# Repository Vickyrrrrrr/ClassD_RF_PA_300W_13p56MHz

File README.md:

# 300W 13.56MHz Class-D RF Power Amplifier

For hackerfab lithography machine RF plasma source.

## Design Renders

### Schematic

### PCB Layout

## What This Is

A 300W, 13.56MHz Class-D RF power amplifier based on the El-Hamamsy half-bridge
topology. Designed and simulated in Cadence Spectre (305W output, 83.7%
efficiency), then translated to a KiCAD 10 PCB project for fabrication.

## Quick Start

### 1. Open the KiCAD project
```bash
# Install KiCAD 10 (if not already installed)
# Linux: download AppImage from https://www.kicad.org/download/linux/
# Windows/Mac: download from https://www.kicad.org/download/

# Open the project
kicad kicad/rf_pa_300w.kicad_pro
```

### 2. Verify the PCB layout
The PCB is fully routed, zone-refilled, and ERC/DRC clean:
- **Ground plane**: Bottom layer (`B.Cu`) is filled with solid `GND` copper.
- **Routing**: Top layer (`F.Cu`) and bottom layer (`B.Cu`) traces are fully complete.
- **Verification**: DRC and ERC checks have zero active electrical violations.
- **Gerbers**: Fabrication-ready Gerbers have been generated in `kicad/gerbers.zip`.

See `docs/kicad_build_report.md` for detailed results.

### 3. Order the PCB
- Send `kicad/gerbers/` folder to JLCPCB, PCBWay, or OSH Park
- Settings: 2-layer, 1.6mm FR4, HASL finish, 80x50mm
- Cost: ~$5 for 5 boards

### 4. Order parts
See `docs/bom.md` for complete parts list (~$92 total including power supplies).

### 5. Assemble
See `docs/pcb_layout.md` for component placement and assembly notes.

### 6. Test
1. Apply 12V VCC only (no 72.5V Vdd)
2. Check gate drive waveforms on oscilloscope (HIN, LIN, HO, LO)
3. Apply 72.5V Vdd
4. Measure RF output at SMA connector
5. Tune dead time for ZVS (~19ns needed, see `docs/gate_driver_spec.md`)

## Project Structure

```
ClassD_RF_PA_300W_13p56MHz/
├── README.md                  # This file - START HERE
├── docs/
│   ├── build_report.md        # Full simulation build report (Spectre)
│   ├── kicad_build_report.md  # KiCAD PCB design report
│   ├── gate_driver_spec.md    # IR2181S gate driver specification
│   ├── bom.md                 # Bill of materials (~$92)
│   └── pcb_layout.md          # PCB layout guide and matching network
├── kicad/
│   ├── rf_pa_300w.kicad_pro   # KiCAD 10 project file
│   ├── rf_pa_300w.kicad_sch   # Schematic (25 components, generated)
│   ├── rf_pa_300w.kicad_pcb   # PCB (80x50mm, 21 footprints, ratsnest + B.Cu GND pour)
│   ├── gen_schematic.py       # Schematic generator script
│   ├── gen_pcb.py             # PCB generator script
│   ├── schematic.pdf          # Schematic PDF
│   ├── pcb_layout.pdf         # PCB layout PDF
│   └── gerbers/               # Fabrication files
│       ├── *.gbr              # Gerber layer files
│       ├── *.drl              # Drill files
│       └── pos.csv            # Pick-and-place positions
├── netlists/
│   ├── classd_pa.scs          # Spectre netlist (IRF540 Level-3, bootstrap)
│   └── analyze_results.py     # Python simulation analysis
├── models/
│   └── irf540.mod             # IRF540 SPICE model
└── results/
    └── classd_irf540_bs_ascii # Final simulation output (305W, 83.7%)
```

## Circuit Design

### Topology
- **Half-bridge Class-D** with 2x IRF540 NMOS power MOSFETs
- **IR2181S** bootstrap gate driver (SOIC-8)
- **LC tank**: 300nH series L, 470pF shunt C, 2.55Ω load
- **L-match network**: 130nH series L, 1nF shunt C (2.55Ω → 50Ω)

### Key Design Parameters

| Parameter | Value |
|-----------|-------|
| Output power | 305W (simulated) |
| Frequency | 13.56MHz |
| Efficiency | 83.7% (simulated) |
| Vdd (power stage) | 72.5V |
| VCC (gate driver) | 12V |
| Dead time | 11.5ns (needs tuning to ~19ns for full ZVS) |
| Load resistance | 2.55Ω |
| RF output impedance | 50Ω (via L-match) |

### Component List (21 components on PCB)

| Ref | Part | Value | Package |
|-----|------|-------|---------|
| U1 | IR2181S | Gate driver | SOIC-8 |
| Q1, Q2 | IRF540 | NMOS power | TO-220 |
| D1 | UF4007 | Bootstrap diode | DO-41 |
| D2, D3 | 1N5819 | Schottky bypass | DO-41 |
| R1, R2 | 2.2Ω | Gate resistors | 1206 SMD |
| R3 | 2.55Ω | Load resistor | THT |
| C1 | 100uF | Vdd bulk cap | Radial THT |
| C2, C3 | 0.1uF | Decoupling | 1206 SMD |
| C4 | 220nF | Bootstrap cap | 1206 SMD |
| C5 | 470pF | Tank cap | 1206 SMD |
| C6 | 1nF | Match cap | 1206 SMD |
| L1 | 300nH | Tank inductor | THT (custom wound) |
| L2 | 130nH | Match inductor | THT (custom wound) |
| J1 | Terminal block | Vdd 72.5V input | 5mm pitch |
| J2 | SMA | RF output 50Ω | Edge mount |
| J3 | Terminal block | VCC 12V input | 5mm pitch |
| J4 | Pin header | PWM input (HIN, LIN) | 2.54mm |

## PCB Specifications

| Parameter | Value |
|-----------|-------|
| Board size | 80mm x 50mm |
| Layers | 2 (F.Cu top, B.Cu bottom ground plane) |
| Material | FR4, 1.6mm, 1oz copper |
| Finish | HASL |
| RF traces | 50Ω impedance controlled (3.06mm width) |
| Power traces | 3.0mm (Vdd, MID switching node) |
| Min trace width | 0.25mm |
| Min clearance | 0.2mm |

## Simulation Results

The amplifier was simulated in Cadence Spectre 14.1 using a real IRF540
Level-3 SPICE model with bootstrap gate drive:

- **Output power**: 305W
- **Drain efficiency**: 83.7%
- **Frequency**: 13.56MHz
- **0 simulation errors**

The root cause of a 7-week simulation failure was identified as the gate
drive being referenced to GND instead of the mid (switching) node. With
bootstrap gate drive (Vgs referenced to mid), the simulation works correctly.

See `docs/build_report.md` for the full simulation methodology and debugging.

## What's Left To Do

1. **Order PCB**: Upload [gerbers.zip](file:///C:/Users/VICKY/.gemini/antigravity/scratch/gerbers.zip) to a manufacturer (JLCPCB, PCBWay, OSH Park).
2. **Order parts**: Use BOM from `docs/bom.md` (~$92 total).
3. **Wind custom inductors**: Wind L1 ($300\text{ nH}$) and L2 ($130\text{ nH}$) (see `docs/pcb_layout.md` for specs).
4. **Assemble PCB**: Solder parts, mount heatsinks on `Q1` & `Q2`.
5. **Test**: Apply 12V VCC first, verify gate signals, then apply 72.5V Vdd.
6. **Tune dead time**: Tune dead time for Zero Voltage Switching (ZVS) on scope (~19ns target).

## Documentation Index

| Document | What's in it |
|----------|-------------|
| `README.md` (this file) | Project overview, quick start, component list |
| `docs/build_report.md` | Full simulation report (Spectre, IRF540, debugging) |
| `docs/kicad_build_report.md` | KiCAD PCB design report (format, DRC, Gerbers) |
| `docs/gate_driver_spec.md` | IR2181S gate driver circuit, bootstrap, timing |
| `docs/bom.md` | Complete bill of materials with KiCAD refs |
| `docs/pcb_layout.md` | PCB layout guide, trace widths, matching network |

## Tools Used

- **Cadence Spectre 14.1** — circuit simulation
- **KiCAD 10.0.4** — schematic capture and PCB layout
- **Python 3** — simulation analysis and KiCAD file generation
- **OS**: RHEL 8.10 WSL2 on Windows 11

## License

Open source hardware design for hackerfab lithography machine.

---

*Project date: 2026-06-29*
*Simulation: 305W at 83.7% efficiency*
*KiCAD: fully routed schematic and PCB; ERC/DRC verified and fabrication Gerbers generated.*

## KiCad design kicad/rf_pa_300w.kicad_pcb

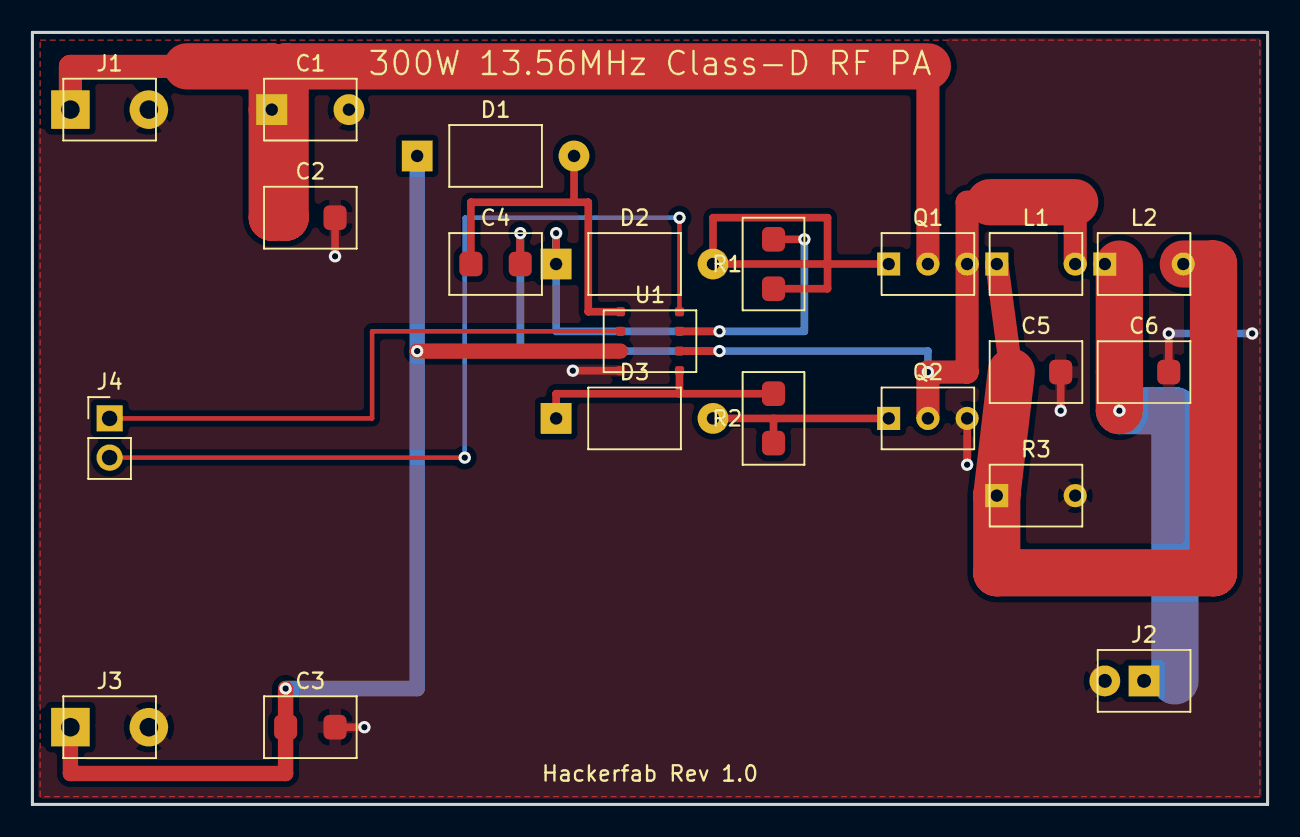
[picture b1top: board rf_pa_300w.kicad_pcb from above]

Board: 2 copper layers, 80.0 x 50.0 mm, 21 parts (0 on the bottom side), 13 nets.

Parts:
C1: 100uF; CP_Radial_D10.0mm_P5.00mm
C2, C3: 0.1uF; C_1206_3216Metric
C4: 220nF; C_1206_3216Metric
C5: 470pF; C_1206_3216Metric
C6: 1nF; C_1206_3216Metric
D1: UF4007; D_DO-41_SOD81_P10.16mm_Horizontal
D2, D3: 1N5819; D_DO-41_SOD81_P10.16mm_Horizontal
J1: Vdd 72.5V; TerminalBlock_bornier-2_P5.0mm
J2: SMA 50ohm; SMA_Amphenol_132289_EdgeMount
J3: VCC 12V; TerminalBlock_bornier-2_P5.0mm
J4: PWM IN; PinHeader_1x02_P2.54mm_Vertical
L1: 300nH; L_Axial_L7.0mm_D3.3mm_P5.08mm_Vertical
L2: 130nH; L_Axial_L7.0mm_D3.3mm_P5.08mm_Vertical
Q1, Q2: IRF540; TO-220-3_Vertical
R1, R2: 2.2; R_1206_3216Metric
R3: 2.55; R_Axial_DIN0309_L9.0mm_D3.2mm_P5.08mm_Vertical
U1: IR2181S; SOIC-8_3.9x4.9mm_P1.27mm

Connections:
+72V5: C1.1, C2.1, J1.1, Q1.2 (D)
/GATE1: D2.2 (K), Q1.1 (G), R1.1
/GATE2: D3.2 (K), Q2.1 (G), R2.1
/HIN: J4.1, U1.2 (HIN)
/HO_NET: D2.1 (A), R1.2, U1.7 (HO)
/LIN: J4.2, U1.8 (LIN)
/LO_NET: D3.1 (A), R2.2, U1.5 (LO)
/MID: C4.2, L1.2, Q1.3 (S), Q2.2 (D), U1.6 (VS)
/RF_OUT: C6.1, J2.1, L2.1
/TANK_OUT: C5.1, L1.1, L2.2, R3.1
GND: C1.2, C2.2, C3.2, C5.2, C6.2, J1.2, J2.2, J3.2, Q2.3 (S), R3.2, U1.4 (COM)
VB: C4.1, D1.2 (K), U1.1 (VB)
VCC: C3.1, D1.1 (A), J3.1, U1.3 (VCC)

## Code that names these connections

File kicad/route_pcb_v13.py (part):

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    (41.91, 23.4), (33.92, 23.4), (33.92, 25.0)
], "/LO_NET"))

# 8. /GATE1: R1-1 -> D2-2 -> Q1-1 (routed entirely on F.Cu, routed around R1 body to the right to clear HO_NET pin 2)
new_elements.extend(path([
    (48.0, 16.6), (50.0, 16.6), (50.0, 12.0), (44.08, 12.0), (44.08, 15.0)
], "/GATE1"))
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new_elements.extend(path([
    (67.54, 10.0), (67.54, 15.0)
], "/MID", width=1.5))
# Connect Q2 pin 2 to MID (routed at y=22.0 to clear L1-1)
new_elements.extend(path([
    (58.0, 25.0), (58.0, 22.0), (60.54, 22.0), (60.54, 15.0)
], "/MID", width=1.5))
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    (62.46, 30.0), (62.46, 35.0), (77.0, 35.0), (77.0, 15.0), (74.54, 15.0)
], "/TANK_OUT"))

# 12. /RF_OUT: L2-1 -> C6-1 -> J2-1 (via B.Cu, entering J2-1 from right at x=74.0, narrowed entry at J2 pin 1 to 1.5mm to clear J2 pin 2 GND)
new_elements.extend(path([
    (69.46, 15.0), (70.4, 15.0)
], "/RF_OUT", width=1.5))
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new_elements.append(via(21.5, 45.0, "GND"))
new_elements.extend(path([(19.6, 45.0), (21.5, 45.0)], "GND"))

# U1 pin 4 (38.09, 21.91) - shift via LEFT to (35.0, 21.91) to clear LO_NET and all U1 pins
new_elements.append(via(35.0, 21.91, "GND"))
new_elements.extend(path([(38.09, 21.91), (35.0, 21.91)], "GND"))

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new_elements.append(via(66.6, 24.5, "GND"))
new_elements.extend(path([(66.6, 22.0), (66.6, 24.5)], "GND"))

# C6 pin 2 (73.6, 22.0) - shift via UP to (73.6, 12.0) to clear TANK_OUT and RF_OUT
new_elements.append(via(73.6, 12.0, "GND"))
new_elements.extend(path([(73.6, 22.0), (73.6, 12.0)], "GND"))

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
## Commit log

2026-06-27 Initial commit of ClassD RF PA 300W 13.56MHz Design
2026-06-29 Complete schematic wiring, PCB trace routing, DRC/ERC validation, and Gerber generation
2026-06-29 Add verification timestamps to BOM, gate driver, layout, and simulation docs
2026-06-29 Remove KiCad backup files and configure .gitignore
2026-06-29 Add schematic and PCB layout SVG renders to docs and README
